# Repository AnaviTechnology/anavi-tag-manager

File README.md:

# ANAVI Tag Manager

ANAVI Tag Manager is an open source hardware development board that acts like a WiFi smart gas detector. It features:

* ESP8266 WiFi microcontroller
* Slot for attaching NFC RFID module
* Dedicated slot for I2C OLED display
* Slots for up to 3 plug and play I2C sensors for temperature, barometric pressure, humidity and light
* UART (Universal asynchronous receiver/transmitter) pins for debugging

Open source software for ANAVI Tag Manager written as an Arduino sketch is also available at GitHub](https://github.com/AnaviTechnology/anavi-tag-manager-sw).

# License

The project is released under the [Creative Commons Attribution-ShareAlike 4.0 International (CC BY-SA 4.0)](https://creativecommons.org/licenses/by-sa/4.0/).

Note: This is a human-readable summary of (and not a substitute for) the [license](https://creativecommons.org/licenses/by-sa/4.0/legalcode).

You are free to:

Share — copy and redistribute the material in any medium or format Adapt — remix, transform, and build upon the material for any purpose, even commercially. The licensor cannot revoke these freedoms as long as you follow the license terms. Under the following terms:

Attribution — You must give appropriate credit, provide a link to the license, and indicate if changes were made. You may do so in any reasonable manner, but not in any way that suggests the licensor endorses you or your use. ShareAlike — If you remix, transform, or build upon the material, you must distribute your contributions under the same license as the original. No additional restrictions — You may not apply legal terms or technological measures that legally restrict others from doing anything the license permits. Notices:

You do not have to comply with the license for elements of the material in the public domain or where your use is permitted by an applicable exception or limitation. No warranties are given. The license may not give you all of the permissions necessary for your intended use. For example, other rights such as publicity, privacy, or moral rights may limit how you use the material.

You will have to provide a link to the original creator of the project http://www.anavi.technology on any documentation or website.

Credit can be attributed through a link to the creator website: http://www.anavi.technology

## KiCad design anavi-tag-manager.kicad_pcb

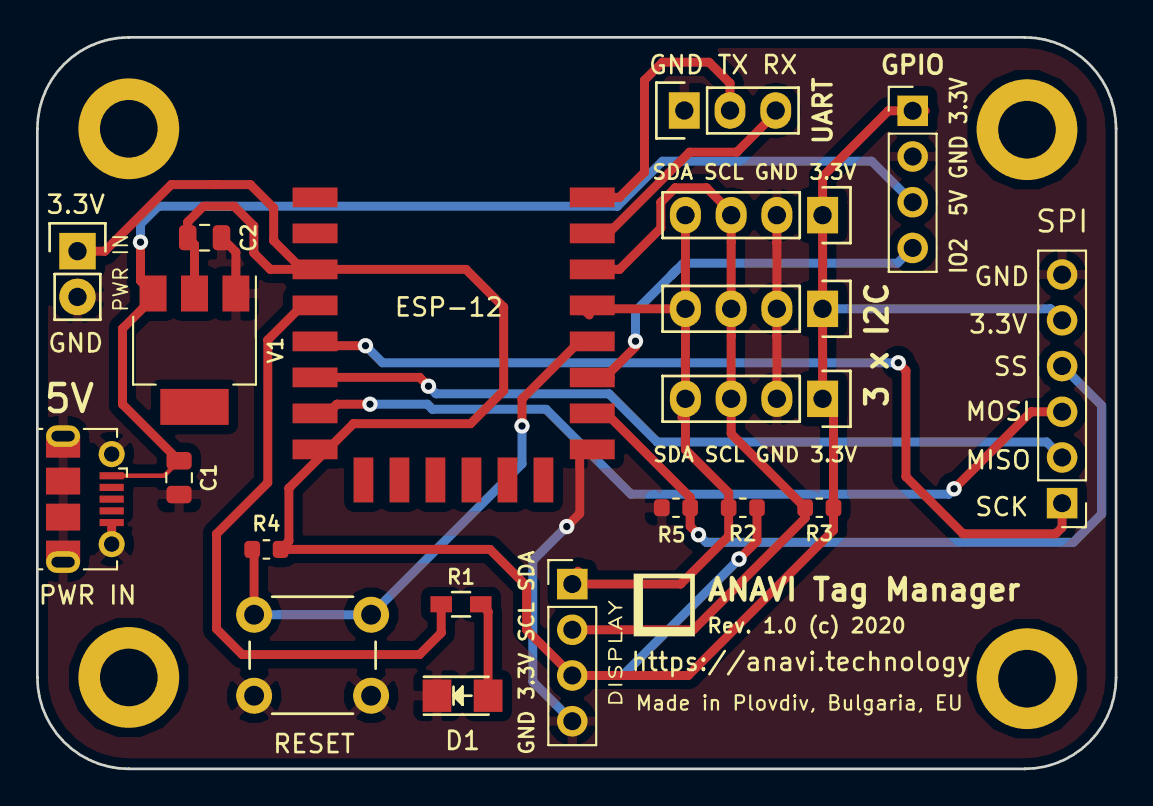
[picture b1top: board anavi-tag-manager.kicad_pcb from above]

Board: 2 copper layers, 59.9 x 40.6 mm, 20 parts (0 on the bottom side), 15 nets.

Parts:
C1, C2: 10uF; C_0805_2012Metric
D1: LED; LED_1206
DISPLAY: Conn_01x04; PinHeader_1x04_P2.54mm_Vertical
ESP-12: ESP-12E; ESP-12E_SMD
GPIO: Conn_01x04; PinHeader_1x04_P2.54mm_Vertical
P1: CONN_01X03; Pin_Header_Straight_1x03
PWR IN: USB_B_Micro; USB_Micro-B_Molex-105017-0001
PWR IN#2: Conn_01x02; Pin_Header_Straight_1x02
R1: 68R; R_0603_HandSoldering
R2, R3: 4,7K; R_0603_1608Metric
R4, R5: 2K; R_0603_1608Metric
RESET: SW_DIP_x01; SW_PUSH_6mm_h4.3mm
SPI: Conn_01x06; PinHeader_1x06_P2.54mm_Vertical
U1, U2, U3: I2C_SENS_1; Pin_Header_Straight_1x04
V1: LD1117S33TR; SOT-223

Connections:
+3V3: C2.1, DISPLAY.3, ESP-12.3, ESP-12.8, GPIO.1, PWR IN#2.1, R2.1, R3.1, R4.2, SPI.5, U1.1, U2.1, U3.1, V1.2
+5V: C1.1, GPIO.3, PWR IN.1, V1.3
GND: C1.2, C2.2, D1.1, DISPLAY.4, ESP-12.9, GPIO.2, P1.1, PWR IN.5, PWR IN.6, PWR IN#2.2, R5.2, RESET.1, SPI.6, U1.2, U2.2, U3.2, V1.1
unnamed: D1.2, R1.2
unnamed: ESP-12.4, R1.1
unnamed: ESP-12.5, SPI.1
unnamed: ESP-12.6, SPI.2
unnamed: ESP-12.7, SPI.3
unnamed: ESP-12.10, R5.1, SPI.4
unnamed: ESP-12.11, GPIO.4
unnamed: ESP-12.12, R4.1, RESET.2
unnamed: DISPLAY.1, ESP-12.13, R2.2, U1.4, U2.4, U3.4
unnamed: DISPLAY.2, ESP-12.14, R3.2, U1.3, U2.3, U3.3
unnamed: ESP-12.15, P1.3
unnamed: ESP-12.16, P1.2

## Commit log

2020-01-04 Initial commit
    The design of the printed circuit board for ANAVI Tag Manager
    is based on ANAVI Gas Detector and ANAVI Thermometer.
2020-01-04 anavi-tag-manager.sch: Modify schematics
    Remove unnecessary components inherited by ANAVI Gas Detector.
    Add 4.7K resistor to GPIO15 of ESP8266. This way it is possible
    to use this pin for SPI communicaiton after booting the board:
    https://github.com/esp8266/Arduino/issues/2466#issuecomment-330794960
2020-01-04 anavi-tag-manager.sch: Add SPI connector
    Add a connector with 6 pins for SPI.
2020-01-05 anavi-tag-manager.kicad_pcb: Clear old tracks
    Clear old tracks and prepare for net list import.
2020-01-05 anavi-tag-manager.sch: Add 3.3V & assign footprints
    Add an alternative 3.3V input for power supply from batteries.
    Assign footprints to components.
2020-01-05 anavi-tag-manager.kicad_pcb: Move components
    Move I2C slots and GPIO pins to save some space.
2020-01-05 anavi-tag-manager.kicad_pcb: Import netlist
2020-01-05 anavi-tag-manager.kicad_pcb: PCB routing
    Apart from the routing, also change the position of GND on the
    GPIO header (with IO2). The new order makes connecting servo
    motors easier because the yellow wire should go to IO2, red wire
    to 5V and black wire to GND.
2020-01-06 anavi-tag-manager.kicad_pcb: Adjust positions
    Adjust positions of components.
2020-02-20 anavi-tag-manager.kicad_pcb: Set R5 to 2K
    Change R5 value from 4.7K to 2K to ensure that the PN532 NFC
    module will not affect the initial state of GPIO15 on booting.

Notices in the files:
anavi-tag-manager.kicad_pcb:
Rev. 1.0 (c) 2020
